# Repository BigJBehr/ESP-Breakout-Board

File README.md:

# ESP Breakout Board
These are the Eagle files required to have one of these boards made by a PCB manufacturer.
The file ESP32 Board.png is a picture of the assembled board with an ESP32 Dev Kit.
The .zip file contains all the files required by the PCB manufacturer.
The .sch file is the Egle schematic of the board.
The .pdf is a pdf version of the schematic.
The .brd file is the Eagle PCB layout file.
me.lbr is my personal Eagle library. You may need to include this if you modify the schematic or layout as it has the part footprints and symbols.

## This is a collection of three boards manufactured as one board
When you receive these boards you will have to cut them apart to get the three individual boards. There are not guide lines as to where to cut. I use a bandsaw with a metal utting blade to cut them apart. A hacksaw or razor saw will work.

### The ESP Breakout Board
The ESP breakout board can accomodate an ESP8266 dev kit or one of the older ESP32 dev kits that have two rows of fifeteen pins. Newer ESP32 boards use 18 or more pins per row. These will not fit this board.

Each row of GPIO pins has a row of ground pins and a row of 3.3V pins.

The ESP Breakout board has a tri-color LED with current limiting resistors. The LED is accessed by a three pin header. You can use female-to-female jumber cables to wire the LED to any GPIO pin on your dev kit. The LED is common anode, so a low level on the GPIO pin will light up the LED.

The board has a single pushbutton switch with a pullup resistor. A one pin header is used to access the switch. The switch will be normally high and will go low when pressed. You can wire it to the GPIO pin of your choice.

A three pin header/socket is provided for an IR detector or any 3.3V sensor of your choice.  single header pin is provided for wireing to the sensor.

There are pads under the dev kit that can be used to solder down a AS1117 3.3V regulator and associated capacitors (10uf, 10V, Tantalum). The regulator is only needed if your 3.3V loads will exceed the 1 amp capability of the 3.3V regulator on the dev kit. The regulator gets its input voltage from the 5V on the USB interface or the Vin pin of the dev kit. If you install the regulator then you should also isolate the 3.3V pin from the dev kit. This can be done by cutting the trace on the bottom of the board.

This board can also be assembled to work with Witty ESP8266 boards. Witty boards have two rows of eight pins that are 1.2 inches apart. You will need to program the Witty ESP8266 using the mating board that came with it. No provision is made tp program Witty boards in circuit.

### IR Blaster board
This is a simple IR Blaster board. It has an onboard FET the switches the IR LED array on/off. The FET is required due to the high power used by the IR LED array. Six IR LEDs are arranged in an ARC. The IR LEDs used are high power (100ma) and have a fairly wide signal cone. The arrangment is ment to provide the widest possible IR coverage. The board uses 5V to power the LEDs. The LEDs are wired as two in series with a current limiting resistor. Three sets of LEDs are on the board. This board can be used with any microcontroller. Keep in mind that if you use the LEDs called out in the schematic then the board will draw about 300ma when the LEDs are turned on. You can substitute lower power IR LEDs, in which case you will need to adjust the value of the current limiting resistors. You can also reduce the number of LEDs in the array to reduce power.

### HM-11 Breakout Board
This is a breakout board for an HM-11 Bluetooth module. The module is soldered directly to the brakout board. All of the pins of the module are broken out. You can use this board to connect an HC-11 module to any 3.3V microcontroller. The board has a  regulator to drop the 5V input to 3.3V for the HC-11. The GPIO of the HC-11 does not have any level translators. Make sure you only connect to 3.3V devices. Biasing resistors have been added to the inputs that require them. A status LED is provided.

### Misc.
All surface mount resistors are 1206 footprint. The tri-color LED is through-hole, common anode. The resistors on the IR Blaster are 20 ohm, 1/2 Watt thrrough-hole.

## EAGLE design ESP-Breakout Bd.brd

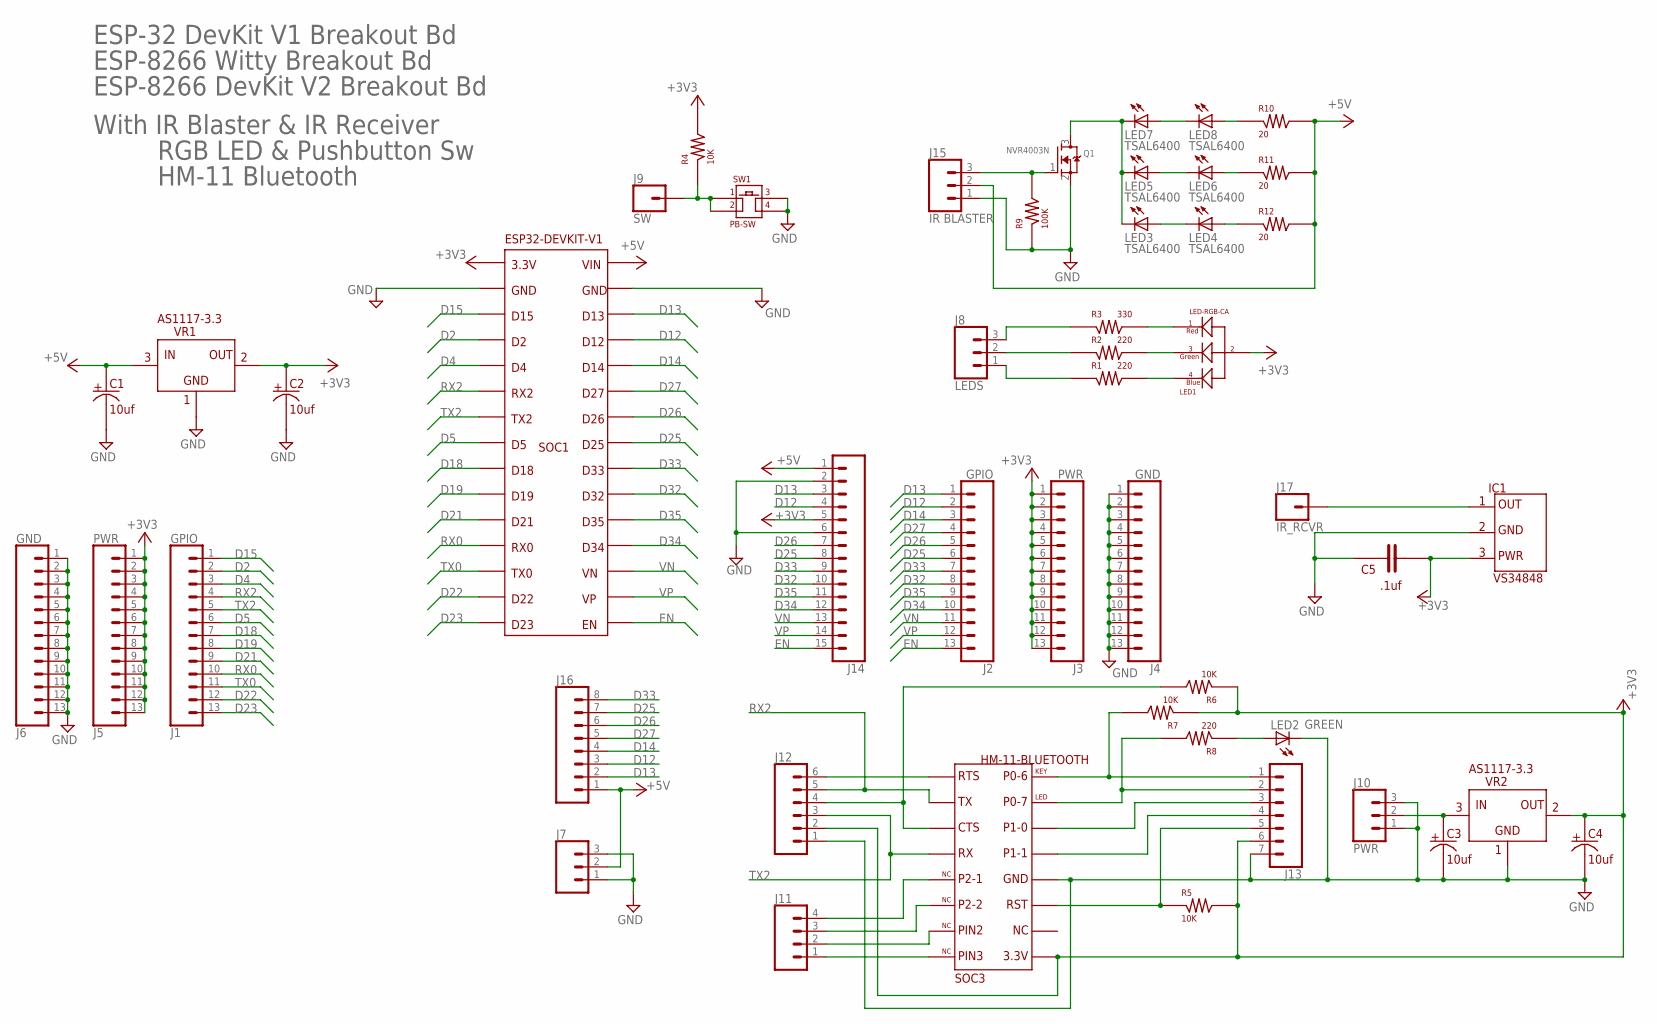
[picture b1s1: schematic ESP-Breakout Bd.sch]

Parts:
C1, C2, C3, C4: 10uf; SMT-B
C5: .1uf; CAP-2.5MM-ROUND
IC1: VS34848; VS34838
J1, J2: GPIO; 1X13
J3, J5: PWR; 1X13
J4, J6: GND; 1X13
J7: CONN_03; 1X03
J8: LEDS; 1X03
J9: SW; 1X01
J10: PWR; 1X03
J11: CONN_04; 1X04
J12: CONN_06SILK_FEMALE_PTH; 1X06
J13: CONN_07; 1X07
J14: CONN_15; 1X15
J15: IR BLASTER; 1X03
J16: CONN_08"; 1X08
J17: IR_RCVR; 1X01
LED1: LED-RGB-CA; LED-RGB-5MM
LED2: GREEN; CHIPLED_0805
LED3, LED4, LED5, LED6, LED7, LED8: TSAL6400; LED5MM
Q1: NVR4003N; SOT23
R1, R2: 220; SMT-1206-TOP
R3: 330; SMT-1206-TOP
R4: 10K; SMT-1206-TOP
R5, R6, R7: 10K; SMT-0603
R8: 220; SMT-0603
R9: 100K; SMT-0603
R10, R11, R12: 20; 1/2WATT
SOC1: ESP32-DEVKIT-V1
SOC3: HM-11-BLUETOOTH; HM-11
SW1: PB-SW
VR1, VR2: AS1117-3.3; SOT-223

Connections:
+3V3: C2.P$1, C4.P$1, C5.P$2 (2), IC1.P$3, J3.1, J3.2, J3.3, J3.4, J3.5, J3.6, J3.7, J3.8, J3.9, J3.10, J3.11, J3.12, J3.13, J5.1, J5.2, J5.3, J5.4, J5.5, J5.6, J5.7, J5.8, J5.9, J5.10, J5.11, J5.12, J5.13, J12.2, J13.6, J14.5, LED1.P$2, R4.P$2, R5.P$2, R6.P$1, R7.P$1, SOC1.P$1, SOC3.P$9, VR1.P$2, VR1.P$4, VR2.P$2, VR2.P$4
+5V: C1.P$1, J7.2, J14.1, J15.2, J16.1, R10.P$2, R11.P$2, R12.P$2, SOC1.P$30, VR1.P$3
D2: J1.2, SOC1.P$4
D4: J1.3, SOC1.P$5
D5: J1.6, SOC1.P$8
D12: J2.2, J14.4, J16.3, SOC1.P$27
D13: J2.1, J14.3, J16.2, SOC1.P$28
D14: J2.3, J16.4, SOC1.P$26
D15: J1.1, SOC1.P$3
D18: J1.7, SOC1.P$9
D19: J1.8, SOC1.P$10
D21: J1.9, SOC1.P$11
D22: J1.12, SOC1.P$14
D23: J1.13, SOC1.P$15
D25: J2.6, J14.8, J16.7, SOC1.P$23
D26: J2.5, J14.7, J16.6, SOC1.P$24
D27: J2.4, J16.5, SOC1.P$25
D32: J2.8, J14.10, SOC1.P$21
D33: J2.7, J14.9, J16.8, SOC1.P$22
D34: J2.10, J14.12, SOC1.P$19
D35: J2.9, J14.11, SOC1.P$20
EN: J2.13, J14.15, SOC1.P$16
GND: C1.P$2, C2.P$2, C3.P$2, C4.P$2, C5.P$1 (1), IC1.P$2, J4.1, J4.2, J4.3, J4.4, J4.5, J4.6, J4.7, J4.8, J4.9, J4.10, J4.11, J4.12, J4.13, J6.1, J6.2, J6.3, J6.4, J6.5, J6.6, J6.7, J6.8, J6.9, J6.10, J6.11, J6.12, J6.13, J7.1, J7.3, J10.1, J10.3, J12.1, J13.7, J14.2, J14.6, J15.1, LED2.C, Q1.2 (S), R9.P$1, SOC1.P$2, SOC1.P$29, SOC3.P$12, SW1.P$3, SW1.P$4, VR1.P$1, VR2.P$1
unnamed: C3.P$1, J10.2, VR2.P$3
unnamed: J13.5, R5.P$1, SOC3.P$11
unnamed: IC1.P$1, J17.1
unnamed: J13.1, R7.P$2, SOC3.P$16
unnamed: J13.2, R8.P$2, SOC3.P$15
unnamed: J12.4, R6.P$2, SOC3.P$3
unnamed: J12.6, SOC3.P$1
unnamed: J11.1, SOC3.P$8
unnamed: J11.2, SOC3.P$7
unnamed: J11.3, SOC3.P$6
unnamed: J11.4, SOC3.P$5
unnamed: J15.3, Q1.1 (G), R9.P$2
unnamed: J13.3, SOC3.P$14
unnamed: J13.4, SOC3.P$13
unnamed: LED2.A, R8.P$1
unnamed: LED7.A, LED8.K (C)
unnamed: LED5.A, LED6.K (C)
unnamed: LED3.A, LED4.K (C)
unnamed: LED3.K (C), LED5.K (C), LED7.K (C), Q1.3 (D)
unnamed: LED8.A, R10.P$1
unnamed: J9.1, R4.P$1, SW1.P$1, SW1.P$2
unnamed: J8.2, R2.P$1
unnamed: LED1.P$3, R2.P$2
unnamed: LED1.P$1, R3.P$2
unnamed: J8.3, R3.P$1
unnamed: J8.1, R1.P$1
unnamed: LED1.P$4, R1.P$2
unnamed: LED6.A, R11.P$1
unnamed: LED4.A, R12.P$1
RX0: J1.10, SOC1.P$12
RX2: J1.4, J12.5, SOC1.P$6, SOC3.P$2
TX0: J1.11, SOC1.P$13
TX2: J1.5, J12.3, SOC1.P$7, SOC3.P$4
VN: J2.11, J14.13, SOC1.P$18
VP: J2.12, J14.14, SOC1.P$17

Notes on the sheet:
ESP-32 DevKit V1 Breakout Bd
ESP-8266 Witty Breakout Bd
ESP-8266 DevKit V2 Breakout Bd
With IR Blaster & IR Receiver
RGB LED & Pushbutton Sw
HM-11 Bluetooth

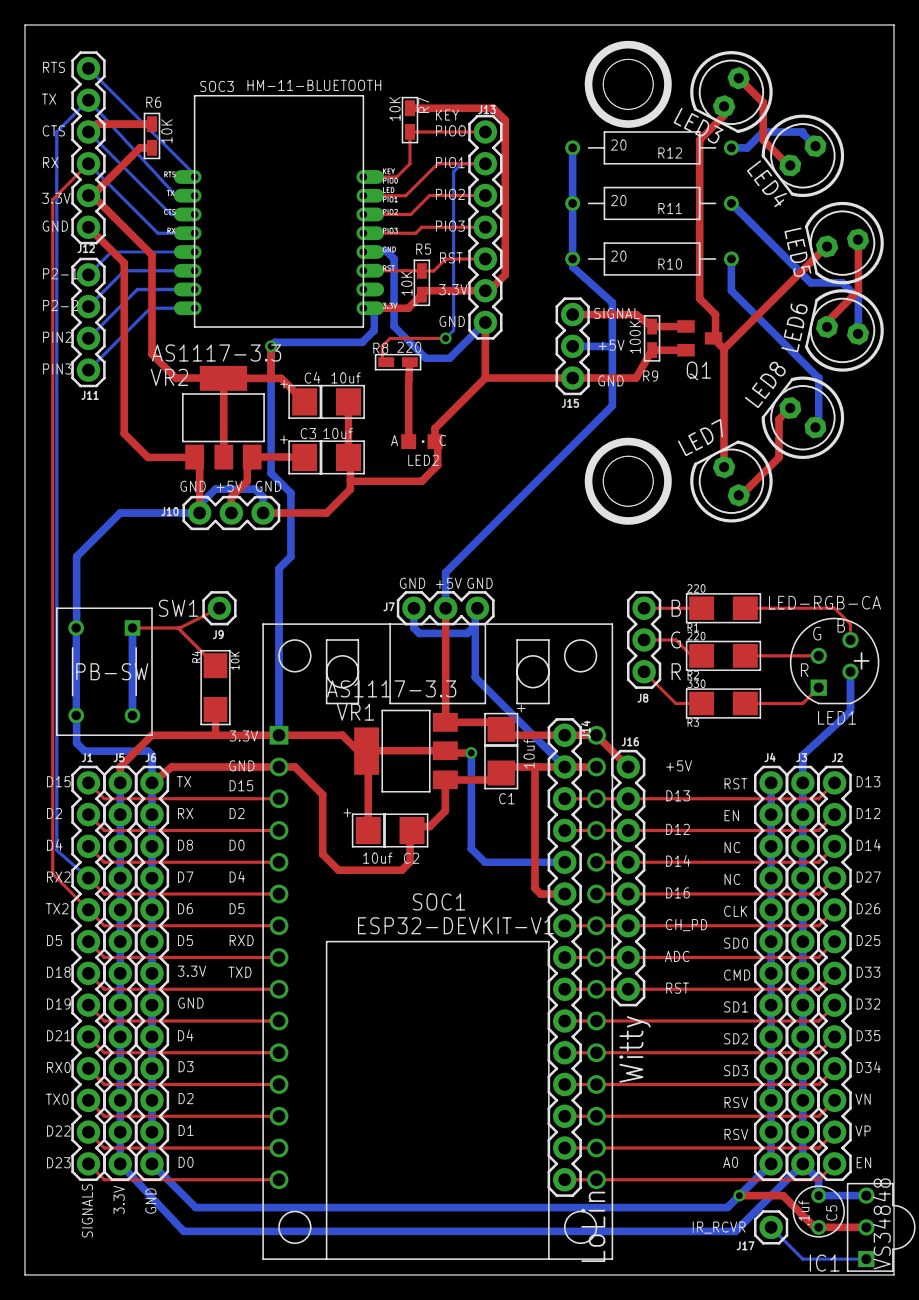
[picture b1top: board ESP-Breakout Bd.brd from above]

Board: 2 copper layers, 69.5 x 100.0 mm, 49 parts (0 on the bottom side), 58 nets.

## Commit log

2018-12-21 Initial release
    All files required to have one of these boards made.

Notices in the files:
parts and their libraries:
SparkFun-Connectors: Licensing: Creative Commons ShareAlike 4.0 International - https://creativecommons.org/licenses/by-sa/4.0
